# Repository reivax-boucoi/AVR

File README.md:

# AVR
Repo for all my AVR-based projects
For more information on this repo feel free to contact the owner

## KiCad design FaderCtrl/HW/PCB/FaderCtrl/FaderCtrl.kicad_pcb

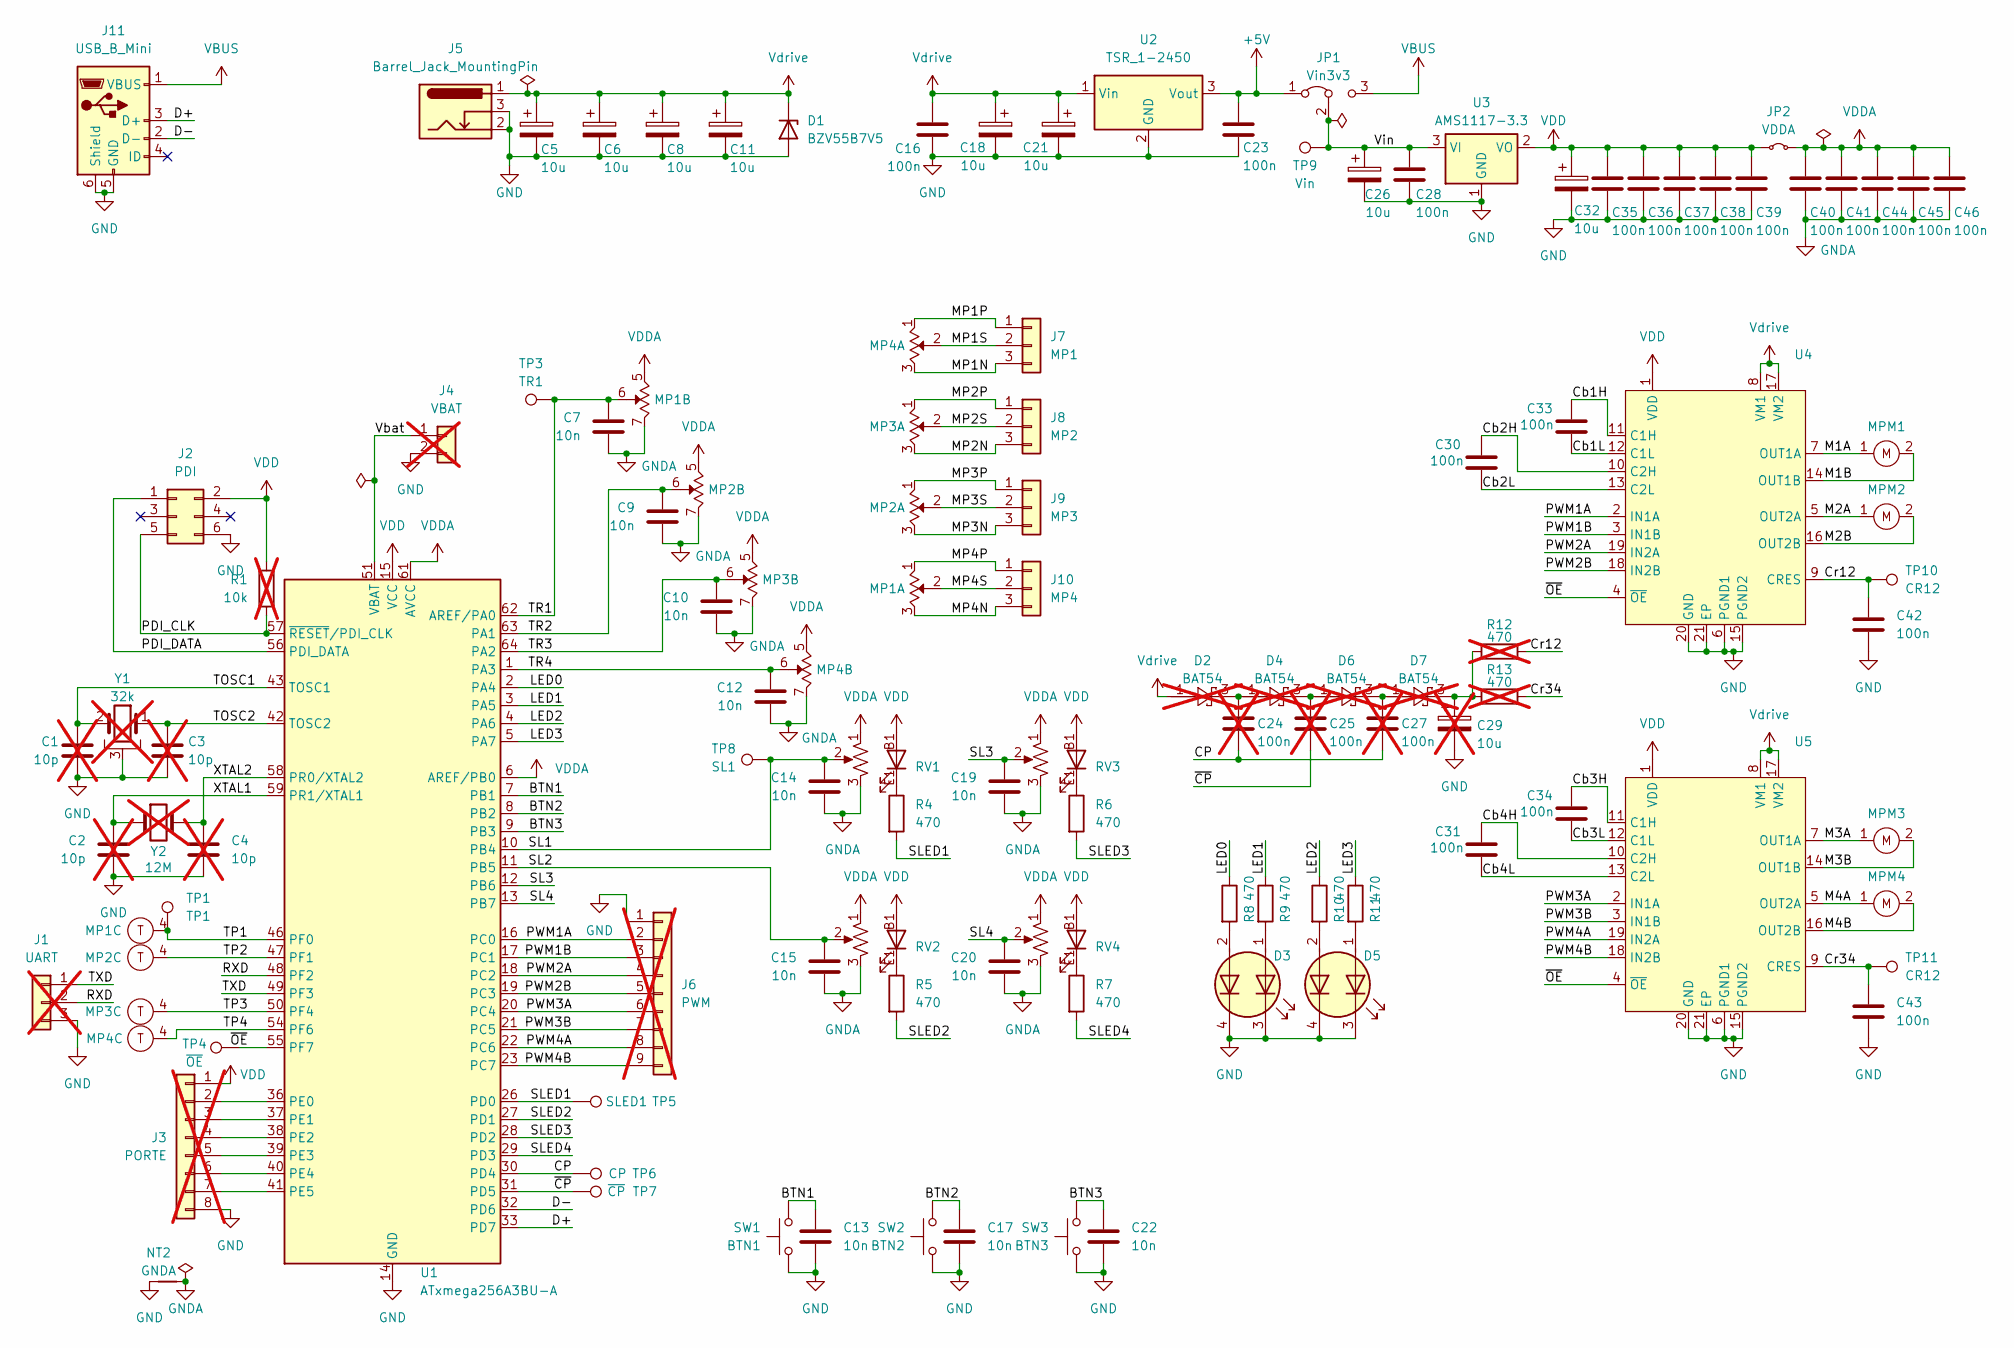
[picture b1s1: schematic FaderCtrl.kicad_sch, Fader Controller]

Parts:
C1, C2, C3, C4: 10p; C_0603_1608Metric_Pad1.08x0.95mm_HandSolder; not fitted
C5, C6, C8, C11, C18, C21, C26, C32: 10u; C_0805_2012Metric_Pad1.18x1.45mm_HandSolder
C7, C9, C10, C12, C13, C14, C15, C17, C19, C20, C22: 10n; C_0603_1608Metric_Pad1.08x0.95mm_HandSolder
C16, C23, C28, C30, C31, C33, C34, C35, C36, C37, C38, C39, C40, C41, C42, C43, C44, C45, C46: 100n; C_0603_1608Metric_Pad1.08x0.95mm_HandSolder
C24, C25, C27: 100n; C_0603_1608Metric_Pad1.08x0.95mm_HandSolder; not fitted
C29: 10u; C_0805_2012Metric_Pad1.18x1.45mm_HandSolder; not fitted
D1: BZV55B7V5; D_MiniMELF
D2, D4, D6, D7: BAT54; SOT-23_Handsoldering; not fitted
D3, D5: LED_Dual_AAKK; LED_Cree-PLCC4_3.2x2.8mm_CCW
J1: UART; PinSocket_1x03_P2.54mm_Vertical; not fitted
J2: PDI; IDC-Header_2x03_P2.54mm_Vertical
J3: PORTE; PinSocket_1x08_P1.27mm_Vertical; not fitted
J4: VBAT; PinSocket_1x02_P2.54mm_Vertical; not fitted
J5: Barrel_Jack_MountingPin; BarrelJack_Horizontal
J6: PWM; PinSocket_1x09_P1.27mm_Vertical; not fitted
J7: MP1; PinHeader_1x03_P2.54mm_Vertical
J8: MP2; PinHeader_1x03_P2.54mm_Vertical
J9: MP3; PinHeader_1x03_P2.54mm_Vertical
J10: MP4; PinHeader_1x03_P2.54mm_Vertical
J11: USB_B_Mini; USB_Mini-B_Wuerth_65100516121_Horizontal
JP1: Vin3v3; SolderJumper-3_P1.3mm_Bridged12_RoundedPad1.0x1.5mm
JP2: VDDA; SolderJumper-2_P1.3mm_Bridged_RoundedPad1.0x1.5mm
MP1, MP2, MP3, MP4: PSM01082A103B2; JST_XH_B7B-XH-A_1x07_P2.50mm_Vertical
MPM1, MPM2, MPM3, MPM4: PSM01081A103B2_MotorOnly; JST_XH_B2B-XH-A_1x02_P2.50mm_Vertical
NT2: GNDA; NetTie-2_SMD_Pad0.5mm
R1: 10k; R_0603_1608Metric_Pad0.98x0.95mm_HandSolder; not fitted
R4, R5, R6, R7, R8, R9, R10, R11: 470; R_0603_1608Metric_Pad0.98x0.95mm_HandSolder
R12, R13: 470; R_0603_1608Metric_Pad0.98x0.95mm_HandSolder; not fitted
RV1, RV2, RV3, RV4: PTL30-10R0-103B2; PTL6015G0103B2_SlidePotLED
SW1: BTN1; SW_PUSH_6mm_2pins
SW2: BTN2; SW_PUSH_6mm_2pins
SW3: BTN3; SW_PUSH_6mm_2pins
TP1: TP1; TestPoint_Pad_D1.0mm
TP3: TR1; TestPoint_THTPad_D1.0mm_Drill0.5mm
TP4: ~{OE}; TestPoint_THTPad_D1.0mm_Drill0.5mm
TP5: SLED1; TestPoint_Pad_D1.0mm
TP6: CP; TestPoint_Pad_D1.0mm
TP7: ~{CP}; TestPoint_Pad_D1.0mm
TP8: SL1; TestPoint_THTPad_D1.0mm_Drill0.5mm
TP9: Vin; TestPoint_THTPad_D1.0mm_Drill0.5mm
TP10, TP11: CR12; TestPoint_Pad_D1.0mm
U1: ATxmega256A3BU-A; TQFP-64_14x14mm_P0.8mm
U2: TSR_1-2450; Converter_DCDC_TRACO_TSR-1_THT
U3: AMS1117-3.3; SOT-223-3_TabPin2
U4, U5: HTSSOP-20-1EP_4.4x6.5mm_P0.65mm_EP3.4x6.5mm
Y1: 32k; Crystal_C26-LF_D2.1mm_L6.5mm_Horizontal_1EP_style1; not fitted
Y2: 12M; Crystal_SMD_HC49-SD; not fitted

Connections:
+5V: C23.1, JP1.1 (A), U2.3 (Vout)
/BTN1: C13.1, SW1.2, U1.7 (PB1)
/BTN2: C17.1, SW2.2, U1.8 (PB2)
/BTN3: C22.1, SW3.2, U1.9 (PB3)
/CP: C24.2, C27.2, TP6.1, U1.30 (PD4)
/Cb1H: C33.1, U4.11 (C1H)
/Cb1L: C33.2, U4.12 (C1L)
/Cb2H: C30.1, U4.10 (C2H)
/Cb2L: C30.2, U4.13 (C2L)
/Cb3H: C34.1, U5.11 (C1H)
/Cb3L: C34.2, U5.12 (C1L)
/Cb4H: C31.1, U5.10 (C2H)
/Cb4L: C31.2, U5.13 (C2L)
/Cr12: C42.1, R12.2, TP10.1, U4.9 (CRES)
/Cr34: C43.1, R13.2, TP11.1, U5.9 (CRES)
/D+: J11.3 (D+), U1.33 (PD7)
/D-: J11.2 (D-), U1.32 (PD6)
/LED0: R8.1, U1.2 (PA4)
/LED1: R9.1, U1.3 (PA5)
/LED2: R10.1, U1.4 (PA6)
/LED3: R11.1, U1.5 (PA7)
/M1A: MPM1.1 (A), U4.7 (OUT1A)
/M1B: MPM1.2 (B), U4.14 (OUT1B)
/M2A: MPM2.1 (A), U4.5 (OUT2A)
/M2B: MPM2.2 (B), U4.16 (OUT2B)
/M3A: MPM3.1 (A), U5.7 (OUT1A)
/M3B: MPM3.2 (B), U5.14 (OUT1B)
/M4A: MPM4.1 (A), U5.5 (OUT2A)
/M4B: MPM4.2 (B), U5.16 (OUT2B)
/MP1N: J7.3, MP4.3 (1)
/MP1P: J7.1, MP4.1 (3)
/MP1S: J7.2, MP4.2
/MP2N: J8.3, MP3.3 (1)
/MP2P: J8.1, MP3.1 (3)
/MP2S: J8.2, MP3.2
/MP3N: J9.3, MP2.3 (1)
/MP3P: J9.1, MP2.1 (3)
/MP3S: J9.2, MP2.2
/MP4N: J10.3, MP1.3 (1)
/MP4P: J10.1, MP1.1 (3)
/MP4S: J10.2, MP1.2
/PDI_CLK: J2.5, R1.2, U1.57 (~RESET/PDI_CLK)
/PDI_DATA: J2.1, U1.56 (PDI_DATA)
/PWM1A: J6.2, U1.16 (PC0), U4.2 (IN1A)
/PWM1B: J6.3, U1.17 (PC1), U4.3 (IN1B)
/PWM2A: J6.4, U1.18 (PC2), U4.19 (IN2A)
/PWM2B: J6.5, U1.19 (PC3), U4.18 (IN2B)
/PWM3A: J6.6, U1.20 (PC4), U5.2 (IN1A)
/PWM3B: J6.7, U1.21 (PC5), U5.3 (IN1B)
/PWM4A: J6.8, U1.22 (PC6), U5.19 (IN2A)
/PWM4B: J6.9, U1.23 (PC7), U5.18 (IN2B)
/RXD: J1.2, U1.48 (PF2)
/SL1: C14.1, RV1.2, TP8.1, U1.10 (PB4)
/SL2: C15.1, RV2.2, U1.11 (PB5)
/SL3: C19.1, RV3.2, U1.12 (PB6)
/SL4: C20.1, RV4.2, U1.13 (PB7)
/SLED1: R4.2, TP5.1, U1.26 (PD0)
/SLED2: R5.2, U1.27 (PD1)
/SLED3: R6.2, U1.28 (PD2)
/SLED4: R7.2, U1.29 (PD3)
/TOSC1: C1.1, U1.43 (TOSC1), Y1.2
/TOSC2: C3.1, U1.42 (TOSC2), Y1.1
/TP1: MP1.4 (T), TP1.1, U1.46 (PF0)
/TP2: MP2.4 (T), U1.47 (PF1)
/TP3: MP3.4 (T), U1.50 (PF4)
/TP4: MP4.4 (T), U1.54 (PF6)
/TR1: C7.1, MP1.6 (2'), TP3.1, U1.62 (AREF/PA0)
/TR2: C9.1, MP2.6 (2'), U1.63 (PA1)
/TR3: C10.1, MP3.6 (2'), U1.64 (PA2)
/TR4: C12.1, MP4.6 (2'), U1.1 (PA3)
/TXD: J1.1, U1.49 (PF3)
/Vbat: J4.1, U1.51 (VBAT)
/Vin: C26.1, C28.1, JP1.2 (C), TP9.1, U3.3 (VI)
/XTAL1: C2.1, U1.59 (PR1/XTAL1), Y2.1
/XTAL2: C4.1, U1.58 (PR0/XTAL2), Y2.2
/~CP: C25.2, TP7.1, U1.31 (PD5)
/~OE: TP4.1, U1.55 (PF7), U4.4 (~OE), U5.4 (~OE)
GND: C1.2, C2.2, C3.2, C4.2, C5.2, C6.2, C8.2, C11.2, C13.2, C16.2, C17.2, C18.2, C21.2, C22.2, C23.2, C26.2, C28.2, C29.2, C32.2, C35.2, C36.2, C37.2, C38.2, C39.2, C42.2, C43.2, D1.2 (A), D3.3 (K1), D3.4 (K2), D5.3 (K1), D5.4 (K2), J1.3, J2.6, J3.8, J4.2, J5.2, J5.3, J6.1, J11.5 (GND), J11.6 (Shield), NT2.1, SW1.1, SW2.1, SW3.1, U1.14 (GND), U1.24 (GND), U1.34 (GND), U1.44 (GND), U1.52 (GND), U1.60 (GND), U2.2 (GND), U3.1 (GND), U4.6 (PGND1), U4.15 (PGND2), U4.20 (GND), U4.21 (EP), U5.6 (PGND1), U5.15 (PGND2), U5.20 (GND), U5.21 (EP), Y1.3
GNDA: C7.2, C9.2, C10.2, C12.2, C14.2, C15.2, C19.2, C20.2, C40.2, C41.2, C44.2, C45.2, C46.2, MP1.7 (3'), MP2.7 (3'), MP3.7 (3'), MP4.7 (3'), NT2.2, RV1.3, RV2.3, RV3.3, RV4.3
unnamed: C24.1, D2.3, D4.1
unnamed: C25.1, D4.3, D6.1
unnamed: C27.1, D6.3, D7.1
unnamed: C29.1, D7.3, R12.1, R13.1
unnamed: D3.1 (A1), R9.2
unnamed: D3.2 (A2), R8.2
unnamed: D5.1 (A1), R11.2
unnamed: D5.2 (A2), R10.2
unnamed: J3.2, U1.36 (PE0)
unnamed: J3.3, U1.37 (PE1)
unnamed: J3.4, U1.38 (PE2)
unnamed: J3.5, U1.39 (PE3)
unnamed: J3.6, U1.40 (PE4)
unnamed: J3.7, U1.41 (PE5)
unnamed: R4.1, RV1.E1 (E)
unnamed: R5.1, RV2.E1 (E)
unnamed: R6.1, RV3.E1 (E)
unnamed: R7.1, RV4.E1 (E)
VBUS: J11.1 (VBUS), JP1.3 (B)
VDD: C32.1, C35.1, C36.1, C37.1, C38.1, C39.1, J2.2, J3.1, JP2.1 (A), R1.1, RV1.B1 (B), RV2.B1 (B), RV3.B1 (B), RV4.B1 (B), U1.15 (VCC), U1.25 (VCC), U1.35 (VCC), U1.45 (VCC), U1.53 (VCC), U3.2 (VO), U4.1 (VDD), U5.1 (VDD)
VDDA: C40.1, C41.1, C44.1, C45.1, C46.1, JP2.2 (B), MP1.5 (1'), MP2.5 (1'), MP3.5 (1'), MP4.5 (1'), RV1.1, RV2.1, RV3.1, RV4.1, U1.6 (AREF/PB0), U1.61 (AVCC)
Vdrive: C5.1, C6.1, C8.1, C11.1, C16.1, C18.1, C21.1, D1.1 (K), D2.1, J5.1, U2.1 (Vin), U4.8 (VM1), U4.17 (VM2), U5.8 (VM1), U5.17 (VM2)

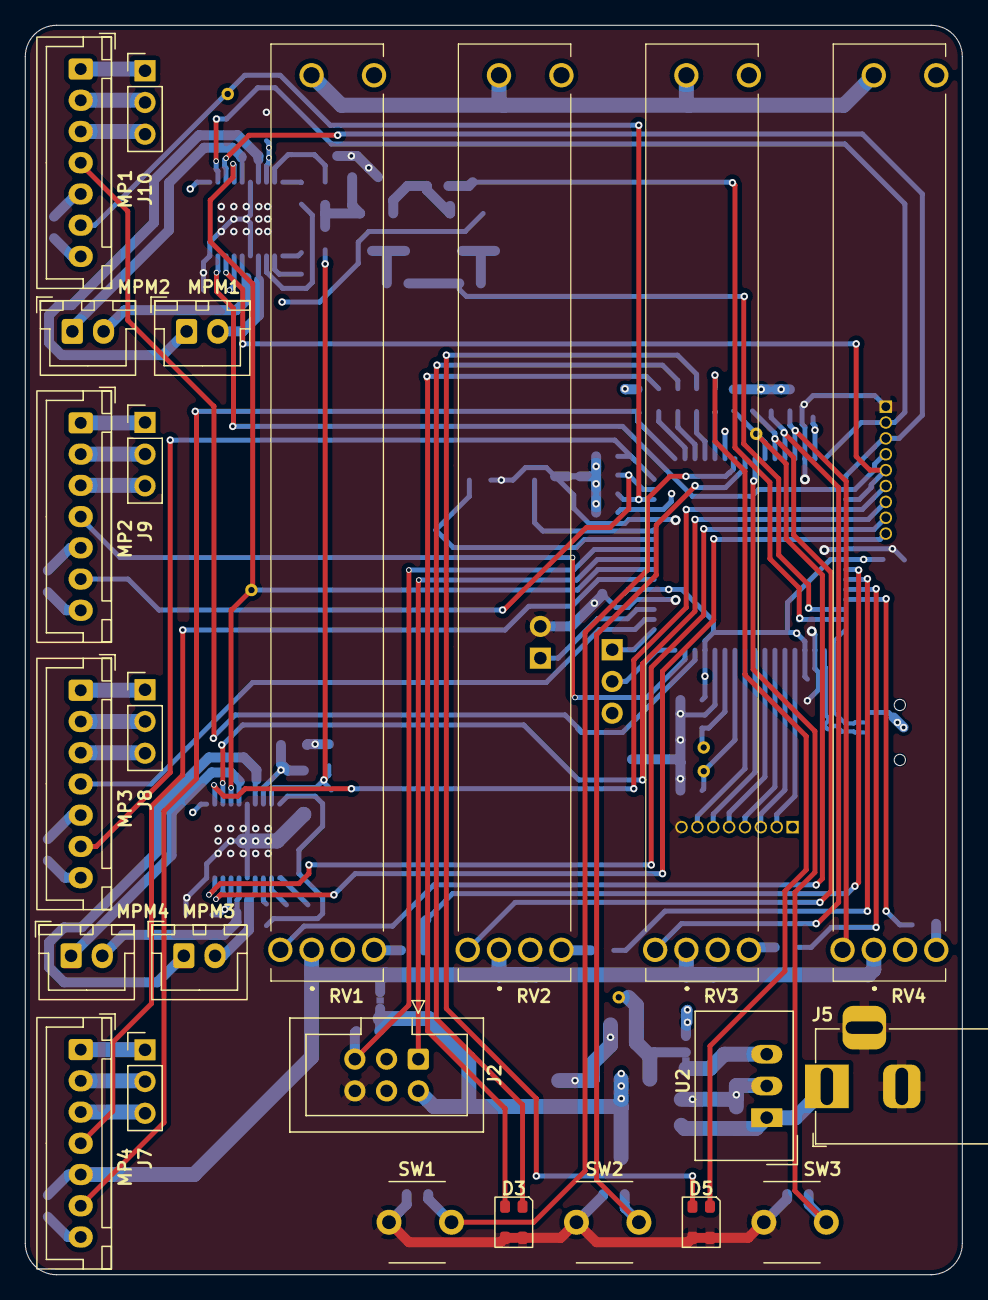
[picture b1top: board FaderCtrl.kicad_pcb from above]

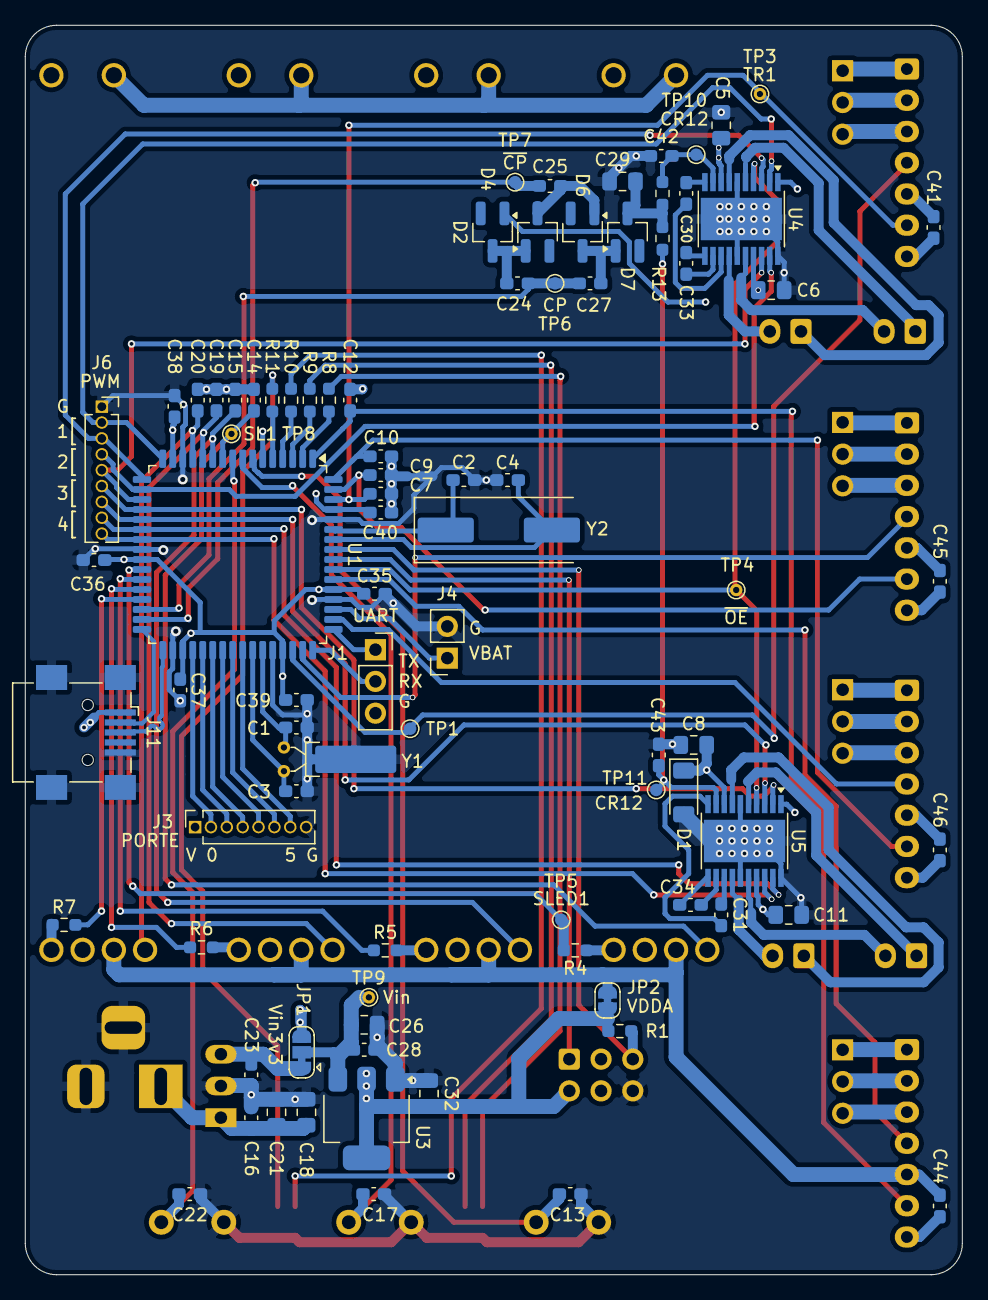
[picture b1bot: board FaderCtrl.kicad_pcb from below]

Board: 4 copper layers, 75.0 x 100.0 mm, 110 parts (86 on the bottom side), 101 nets.

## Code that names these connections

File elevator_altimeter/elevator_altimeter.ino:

#include "Alti.h"

#define NRF_CE PIN_PA0
#define NRF_SCK PIN_PA1
#define NRF_MISO PIN_PA2
#define NRF_IRQ PIN_PA4
#define NRF_MOSI PIN_PA5
#define NRF_CSN PIN_PA6

#define MPL_INT1 PIN_PC2//INT0/PCINT14

#define USER_SW PIN_PC0 //PCINT12 ->PCI2
#define Batt_sense 0 //PIN_PA3->ADC0
#define LED0 PIN_PC4
#define LED1 PIN_PC5

#include <SPI.h>
#include <nRF24L01.h>
#include <RF24.h>

const byte slaveAddress[5] = "XBEA";
uint8_t dataToSend[4] = "OKx"; // etage (4 bits), altitude (18 bits), battery voltage (10 bits)
//[3]: eeeeaaaa [2]: aaaaaaaa [1]: aaaaaabb [0]: bbbbbbbb
RF24 radio(NRF_CE, NRF_CSN);

uint8_t log_mode = 0;
uint16_t batt_v = 0;
Alt_Data alt_data;

void setup() {
    pinMode(LED0, OUTPUT);
    pinMode(LED1, OUTPUT);
    pinMode(USER_SW, INPUT_PULLUP);
    pinMode(MPL_INT1, INPUT);
    pinMode(NRF_CE, OUTPUT);
    pinMode(NRF_SCK, OUTPUT);
    pinMode(NRF_MOSI, OUTPUT);
    pinMode(NRF_CSN, OUTPUT);
    pinMode(NRF_IRQ, INPUT);
    pinMode(NRF_MISO, INPUT);
    Serial.begin(9600);
    Serial.println("Reboot");
    delay(50);
    MPL_init();

    MCUCR = (1 << ISC01); //Interrupt on falling edge of INTO
    GIMSK |= (1 << PCIE2) | (1 << INT0);
    PCMSK2 |= (1 << PCINT12);
    analogReference(DEFAULT);

    radio.begin();
    radio.setDataRate( RF24_250KBPS );
    radio.setRetries(3, 5); // delay, count
    radio.openWritingPipe(slaveAddress);
    Serial.println("Initialized radio !");

}

void loop() {
    if (alt_data.newDataReady) {
        digitalWrite(LED1, HIGH);
        alt_data.newDataReady = false;
        batt_v = analogRead(Batt_sense);// ;
        uint32_t alti;
        uint16_t temp;
        MPL_readAltTemp(&alti, &temp);
        uint8_t etage = alt_data.getEtage(alti);
        /*switch (log_mode) {
            case 0://All: alt,temp,batt
                Serial.print(alti / 16.0); //in meters
                Serial.print(",");
                Serial.print(temp / 16.0); //in degrees C
                Serial.print(",");
                Serial.println(batt_v / 1024.0 * 2.5 * 2.0);
                break;
            case 1://alt only
                Serial.println(alti / 16.0); //in meters
                break;
            case 2://temp only
                Serial.println(temp / 16.0); //in degrees C
                break;
            case 3://batt only
                Serial.println(batt_v / 1024.0 * 2.5 * 2.0);
                break;
            default:
                break;
        }*/
        digitalWrite(LED1, LOW);
        digitalWrite(LED0, HIGH);

        dataToSend[3] = (etage << 4) | ((alti >> 14) & 0x0F);
        dataToSend[2] = alti >> 6;
        dataToSend[1] = ((alti << 2) & 0xFC) | ((batt_v >> 8) & 0x03);
        dataToSend[0] = batt_v;
        if(!radio.write( &dataToSend, sizeof(dataToSend)))Serial.println("Fail");
        digitalWrite(LED0, LOW);
    }
    //GOTO sleep
}

ISR(PCINT2_vect) {

    if (!digitalRead(USER_SW)) {
        if (++log_mode > 4)log_mode = 0;
        Serial.print("Mode :");
        Serial.println(log_mode);
    }
}

ISR(INT0_vect) {
    alt_data.newDataReady = true;
}

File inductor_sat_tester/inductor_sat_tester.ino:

#include <ButtonDebounce.h>

//PB4 - ADC2 : analog in
//PB0 : Button, active low
//PB1 : LED, active HIGH
//PB3 : Output PWM
void buttonChanged(int event);
bool state = true;
int val = 10;
ButtonDebounce button(PB0, 100);
void setup() {
  pinMode(PB1, OUTPUT);
  pinMode(PB2, OUTPUT);
  pinMode(PB4, INPUT);
  pinMode(PB0, INPUT_PULLUP);
  button.setCallback(buttonChanged);
}

void loop() {
  button.update();
  if(state){
    val = analogRead(2)/10;
    digitalWrite(PB2, HIGH);
    delayMicroseconds(val);
    digitalWrite(PB2, LOW);
    delayMicroseconds(10000 - val);
  }
}

void buttonChanged(int event) {
  if (event) {
    state = 1 - state;
    digitalWrite(PB1, state);
  }
  if (!state)digitalWrite(PB2,LOW);
}

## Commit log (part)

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2017-12-06 Create LICENSE
2018-01-16 added new components
2018-01-16 updated project
2018-03-03 added
2018-04-04 khlkjh
2018-04-07 ljhglhjgljhgljhhglhgljhgjuliencombatte
2018-04-15 sdfsfd
2018-04-16 adaaa
2018-04-25 truc
2018-05-01 adazd
2018-05-08 rzrzerz
2018-05-08 erzrzzer
2018-05-08 narrowed down the problem to line 42 of cmds.cpp
2018-05-08 it works
2018-05-08 I should move the interpreter stuff out of the ISR
2018-05-08 I should move the interpreter stuff out of the ISR && fix priorities in transmit
2018-05-15 fsdf
2018-05-15 jhgj
2018-05-16 aeaeze
2018-05-17 Add linker custom linker file base on avr's one
2018-05-17 Add a Makefile for standalone build (w/o Eclipse)
2018-05-17 Set NB_COMMANDS as macro instead of global constant
2018-05-17 Move static definitions from header to source file
2018-05-17 Use strcmp instead of cmd_cmp
2018-05-17 Fix code formatting
2018-05-17 Change UART_BUFFER_SIZE from 256 to 64
2018-05-17 aeazeaez
2018-05-17 fdfs
2018-06-01 dfsdfsf
2018-06-04 azeae
2018-06-27 qseerer
2018-07-04 khjhkjk
2018-07-04 sghdf
2018-07-04 jhgkjhg
2018-07-04 lkjhlkjhlkjh
2018-07-04 kjhk
2018-07-04 working commit
2018-07-04 added dscription support back, without PROGMEM
2018-07-05 functionnal progmem descr
2018-07-06 stream working, changed kill key
2018-07-06 changed flag register to gpior0
2018-07-07 miliohmeter interpreter update
2018-07-07 created m6490
2018-07-07 oci1a on m6490
2018-07-08 m6490 usart
2018-07-12 updated gitignore
2018-07-19 m6490 LCD
2018-07-19 added arrow beg
2018-07-19 ambiguous overload still present
2018-07-19 removed unecessary includes
2018-07-19 bargraph update
2018-07-19 added bargraph default
2018-07-19 cast not fixing overload
2018-07-19 static update
2018-07-19 curly bracket fix
2018-07-19 overload issue
2018-07-19 added charmap
2018-07-19 started pinmap
2018-07-19 map until LCDDR17 not included
2018-07-20 finished rough mapping
2018-07-21 early update
2018-07-23 main.cpp tiny update
2018-09-26 added dumber
2018-11-10 wordclock
2018-11-10 fixed hour issue
2018-12-09 possibly fixed hour not working on midi
2018-12-09 added diagram
2018-12-10 clean
2018-12-11 abandonned leap year correction
2018-12-12 debug removed for release
2018-12-12 fixed color reset status
2018-12-12 half brightness
2018-12-12 todo: check half brigthness
2018-12-13 updated AD5934
2018-12-15 -madded AD5935
2018-12-15 make ad5934
2018-12-15 created eclipse ad5934
2018-12-15 added test class
2018-12-15 added tes_class merge
2018-12-18 created t85_rpime
2018-12-18 updated .project to avr
2019-01-04 deleted unecessary files
2019-01-15 added piezzo project
2019-05-18 modified gitignore
2019-05-20 added gefranclock
2019-09-23 dumber
2019-09-25 keil open
2019-09-26 mv blink->uart_remote
2019-10-07 uart_remote
2019-10-09 ir 328p
2019-10-11 added oled to ltc2992
2020-03-04 added basic sketch
2025-11-04 added heartrate
2025-11-04 added hex src
2025-11-05 added data
2025-11-11 octave parser update
2025-11-11 added octave parser and output logs
2026-01-25 added source
2026-01-25 added example json
2026-01-25 added board schematic
2026-02-14 update adding Temp sensor support
2026-02-14 added temp sensor test
2026-02-15 added DMA basics
2026-02-15 added zit to gitignore
2026-02-15 removed backups
2026-03-04 working
2026-03-04 added .zip to gitignore
